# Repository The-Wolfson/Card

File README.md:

#  Business Card
An NFC PCB business card with LED feedback.

## BOM
|Comment|Part|Quantity|LCSC ID|Price|
|-|-|-|-|-|
NFC Chip|NT3H2111W0FHKH    |1|C710403|$4.43
Capacitor|CL10B224KA8NNNC|1|C21120|$0.56
Resistor|0603WAF470JT5E|1|C23182|$0.11
LED|KT-0805R|3|C2295|$0.53
PCB|5|||$4.00
PCBA|2|||$18.37
Shipping||||$8.14
**Total: $36.14**

## Use
Hold your phone to the card, and the website will open.

## Justification
I need a way to easily point people to my website, this was the solution. A card with a small yet distinct form factor, recognisable even from a distance.

The real  challenge is getting it cheap enough that it can be produced at scale.

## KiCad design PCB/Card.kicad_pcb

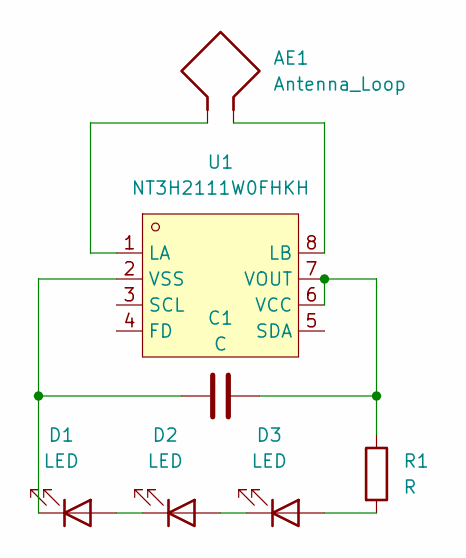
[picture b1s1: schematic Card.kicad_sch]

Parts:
AE1: Antenna_Loop; NFC_Antenna
C1: C; C0603
D1, D2, D3: LED; LED0805-R-RD
R1: R; R0603
U1: NT3H2111W0FHKH; XQFN-8_L1.6-W1.6-P0.50-BL_NT3H2111W0FHKH; LCSC Part C710403

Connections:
unnamed: D1.2 (A), D2.1 (K)
unnamed: C1.1, D1.1 (K), U1.2 (VSS)
unnamed: D2.2 (A), D3.1 (K)
unnamed: D3.2 (A), R1.2
unnamed: AE1.1, U1.1 (LA)
unnamed: AE1.2, U1.8 (LB)
unnamed: C1.2, R1.1, U1.6 (VCC), U1.7 (VOUT)

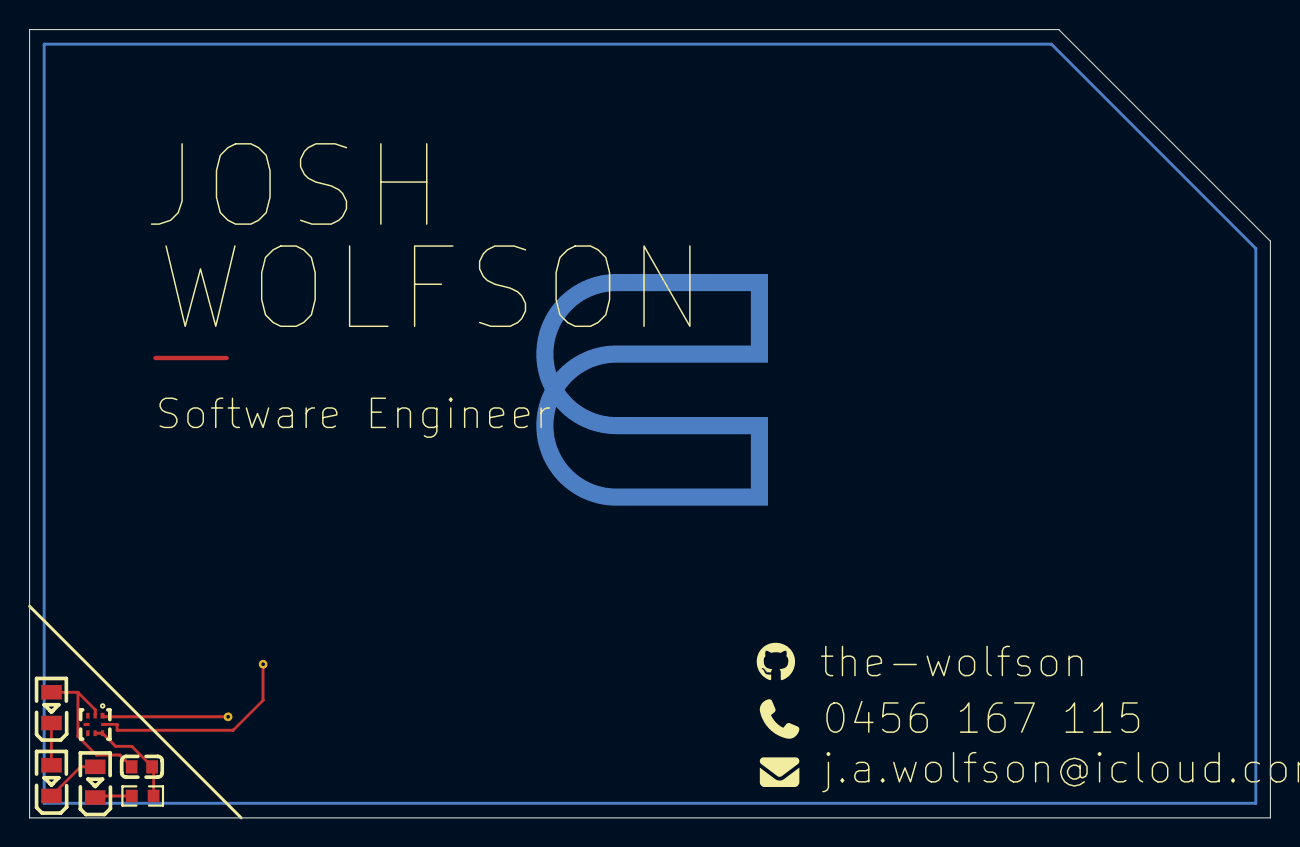
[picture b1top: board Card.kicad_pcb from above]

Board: 2 copper layers, 85.0 x 54.0 mm, 7 parts (1 on the bottom side), 7 nets.

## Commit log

2025-07-26 updated PCB
